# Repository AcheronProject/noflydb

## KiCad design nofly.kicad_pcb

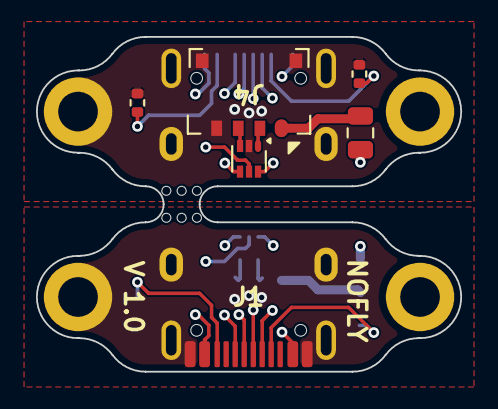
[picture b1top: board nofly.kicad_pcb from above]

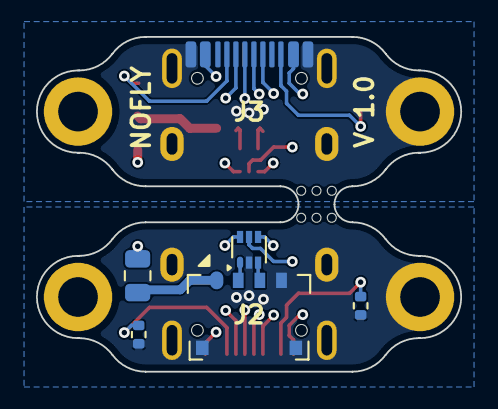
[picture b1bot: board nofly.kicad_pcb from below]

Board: 4 copper layers, 23.6 x 18.6 mm, 18 parts (8 on the bottom side), 9 nets.

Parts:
B1, B2: MouseBite; MouseBite-Part_2.0x2.0mm_outset_D0.5mm_P0.85mm_3h
F1, F2: SMD0805-050; Fuse_0805_2012Metric
H1, H1#2, H2, H2#2: Mount; MountingHole_2.2mm_M2_DIN965_Pad
J1, J3: TYPE-C-31-M-12; USB_C_Receptacle_Hroparts_TYPE-C-31-M-12
J2, J4: 781710004 / M1201RS-04-BK; MOLEX_PicoEZMate_781710004
R1, R2, R3, R4: 5.1k; R_0402_1005Metric
U1, U2: USBLC6-2P6; SOT-563

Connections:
5V: F1.2, F2.2, J2.1, J4.1
D+: J1.A6 (D+), J1.B6 (D+), J3.A6 (D+), J3.B6 (D+), U1.4 (I/O2), U2.4 (I/O2)
D-: J1.A7 (D-), J1.B7 (D-), J3.A7 (D-), J3.B7 (D-), U1.6 (I/O1), U2.6 (I/O1)
DO+: J2.3, J4.3, U1.3 (I/O2), U2.3 (I/O2)
DO-: J2.2, J4.2, U1.1 (I/O1), U2.1 (I/O1)
GND: H1.1 (MP_1), H1#2.1 (MP_1), J1.A1 (GND), J1.B1 (GND), J1.S (SHIELD), J2.4, J2.MP (MountPin), J3.A1 (GND), J3.B1 (GND), J3.S (SHIELD), J4.4, J4.MP (MountPin), R1.2, R2.2, R3.2, R4.2, U1.2 (GND), U2.2 (GND)
unnamed: J1.A5 (CC1), J3.A5 (CC1), R1.1, R3.1
unnamed: J1.B5 (CC2), J3.B5 (CC2), R2.1, R4.1
VBUS: F1.1, F2.1, J1.A4 (VBUS), J1.B4 (VBUS), J3.A4 (VBUS), J3.B4 (VBUS), U1.5 (VBUS), U2.5 (VBUS)

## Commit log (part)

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2025-07-27 First version
2025-07-27 Organize schematic
2025-07-27 Update component metadata
